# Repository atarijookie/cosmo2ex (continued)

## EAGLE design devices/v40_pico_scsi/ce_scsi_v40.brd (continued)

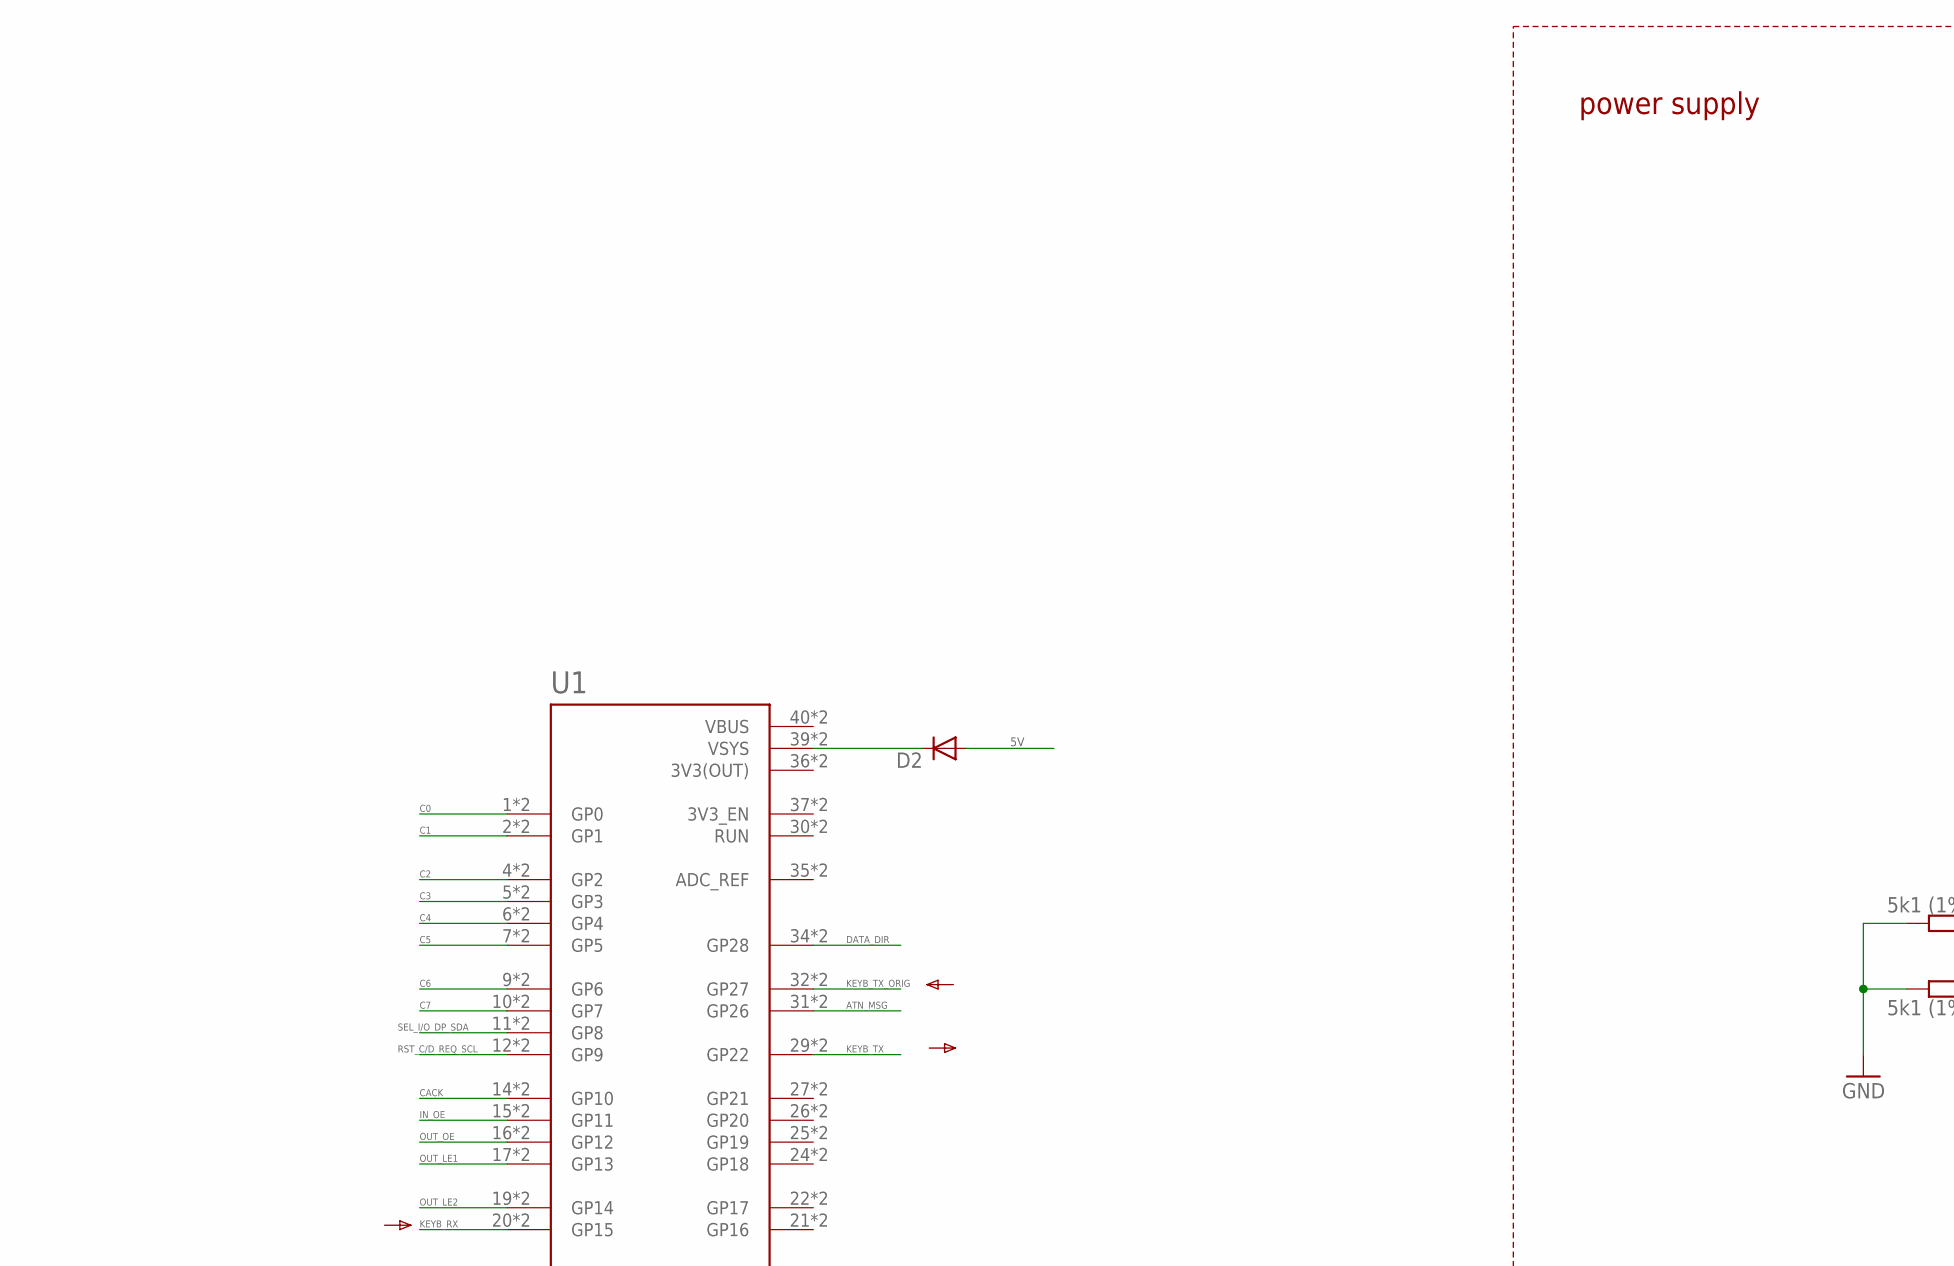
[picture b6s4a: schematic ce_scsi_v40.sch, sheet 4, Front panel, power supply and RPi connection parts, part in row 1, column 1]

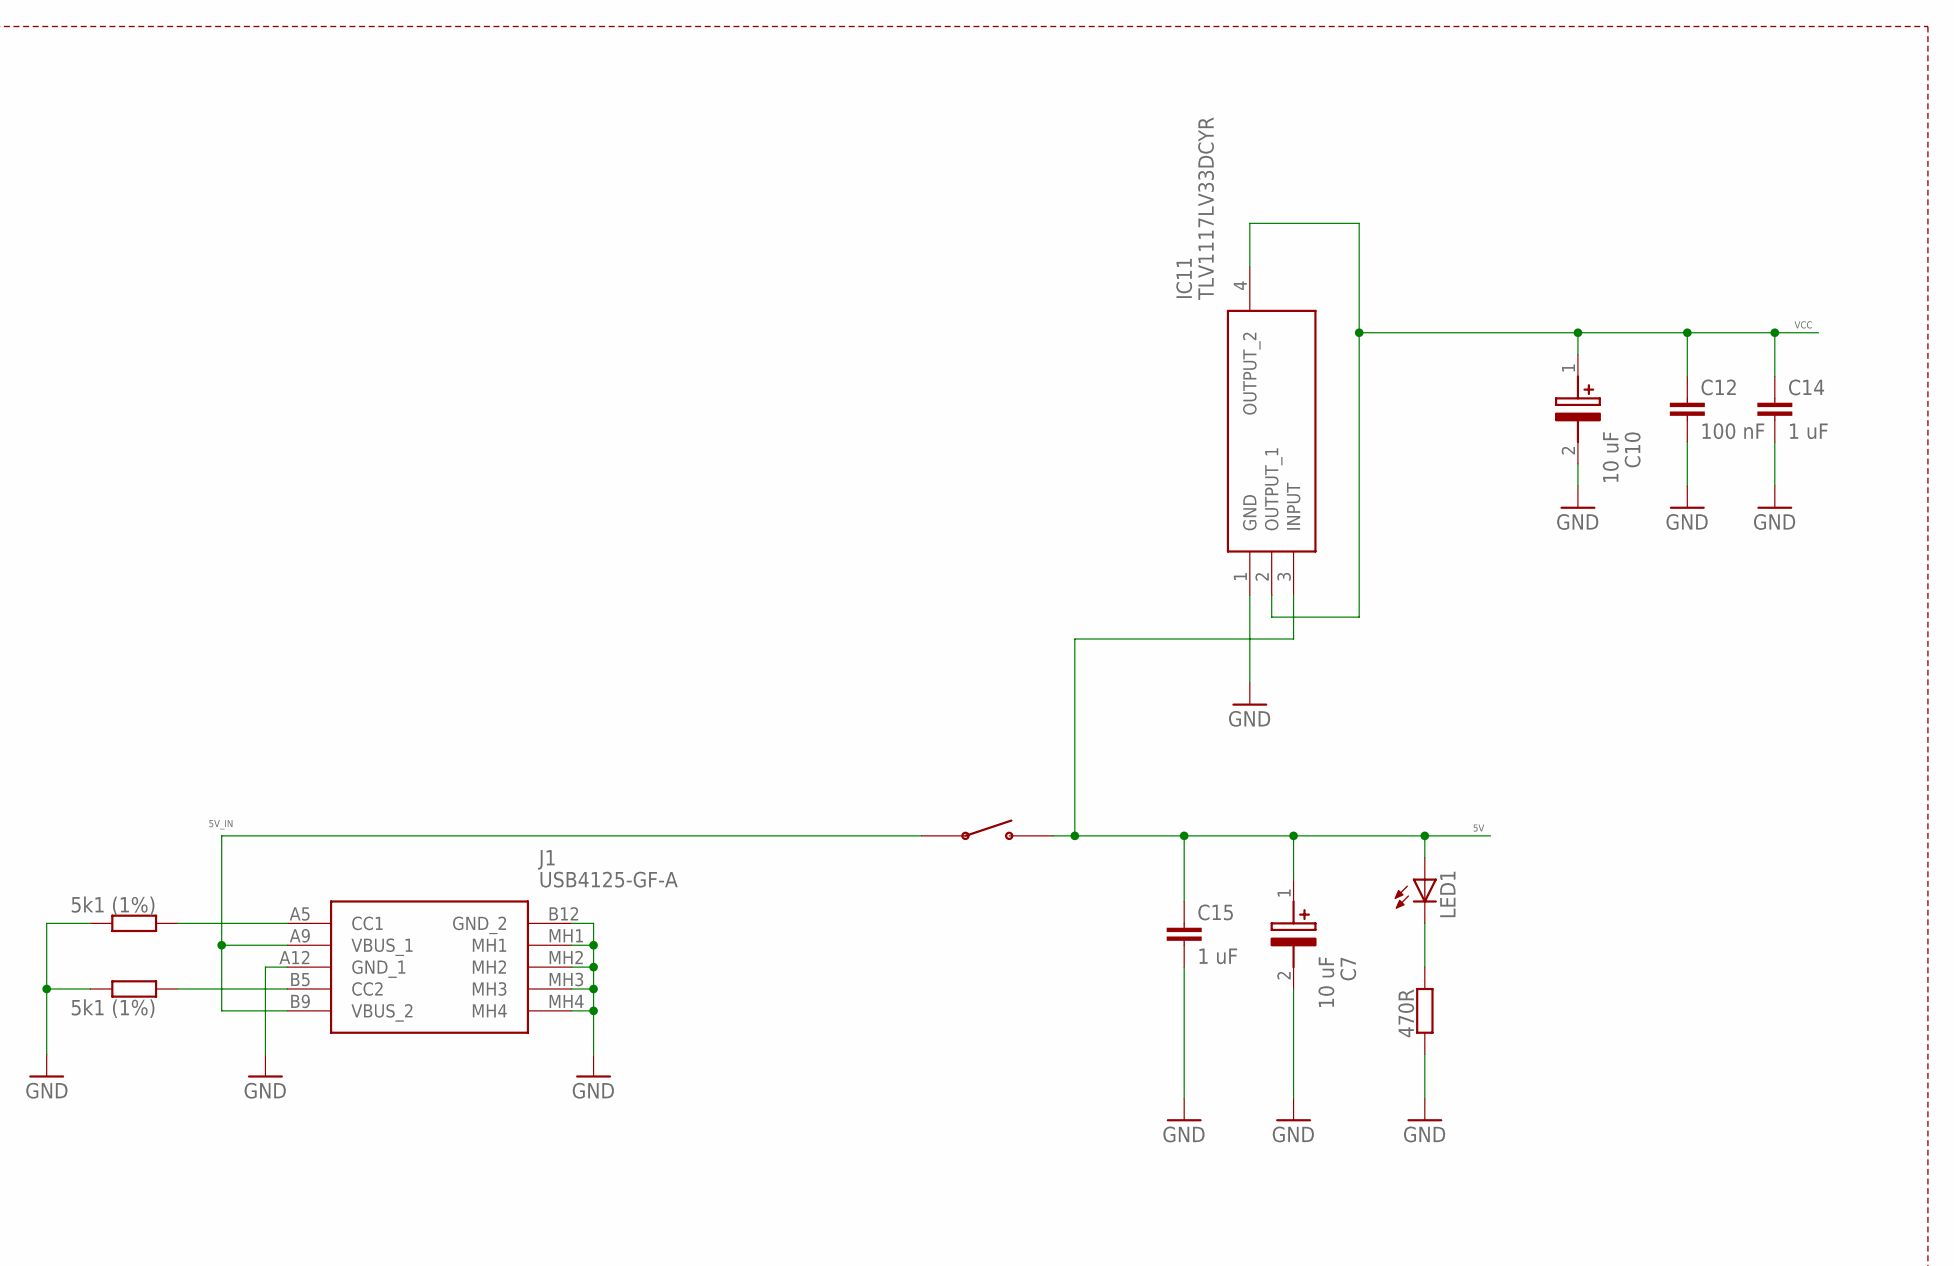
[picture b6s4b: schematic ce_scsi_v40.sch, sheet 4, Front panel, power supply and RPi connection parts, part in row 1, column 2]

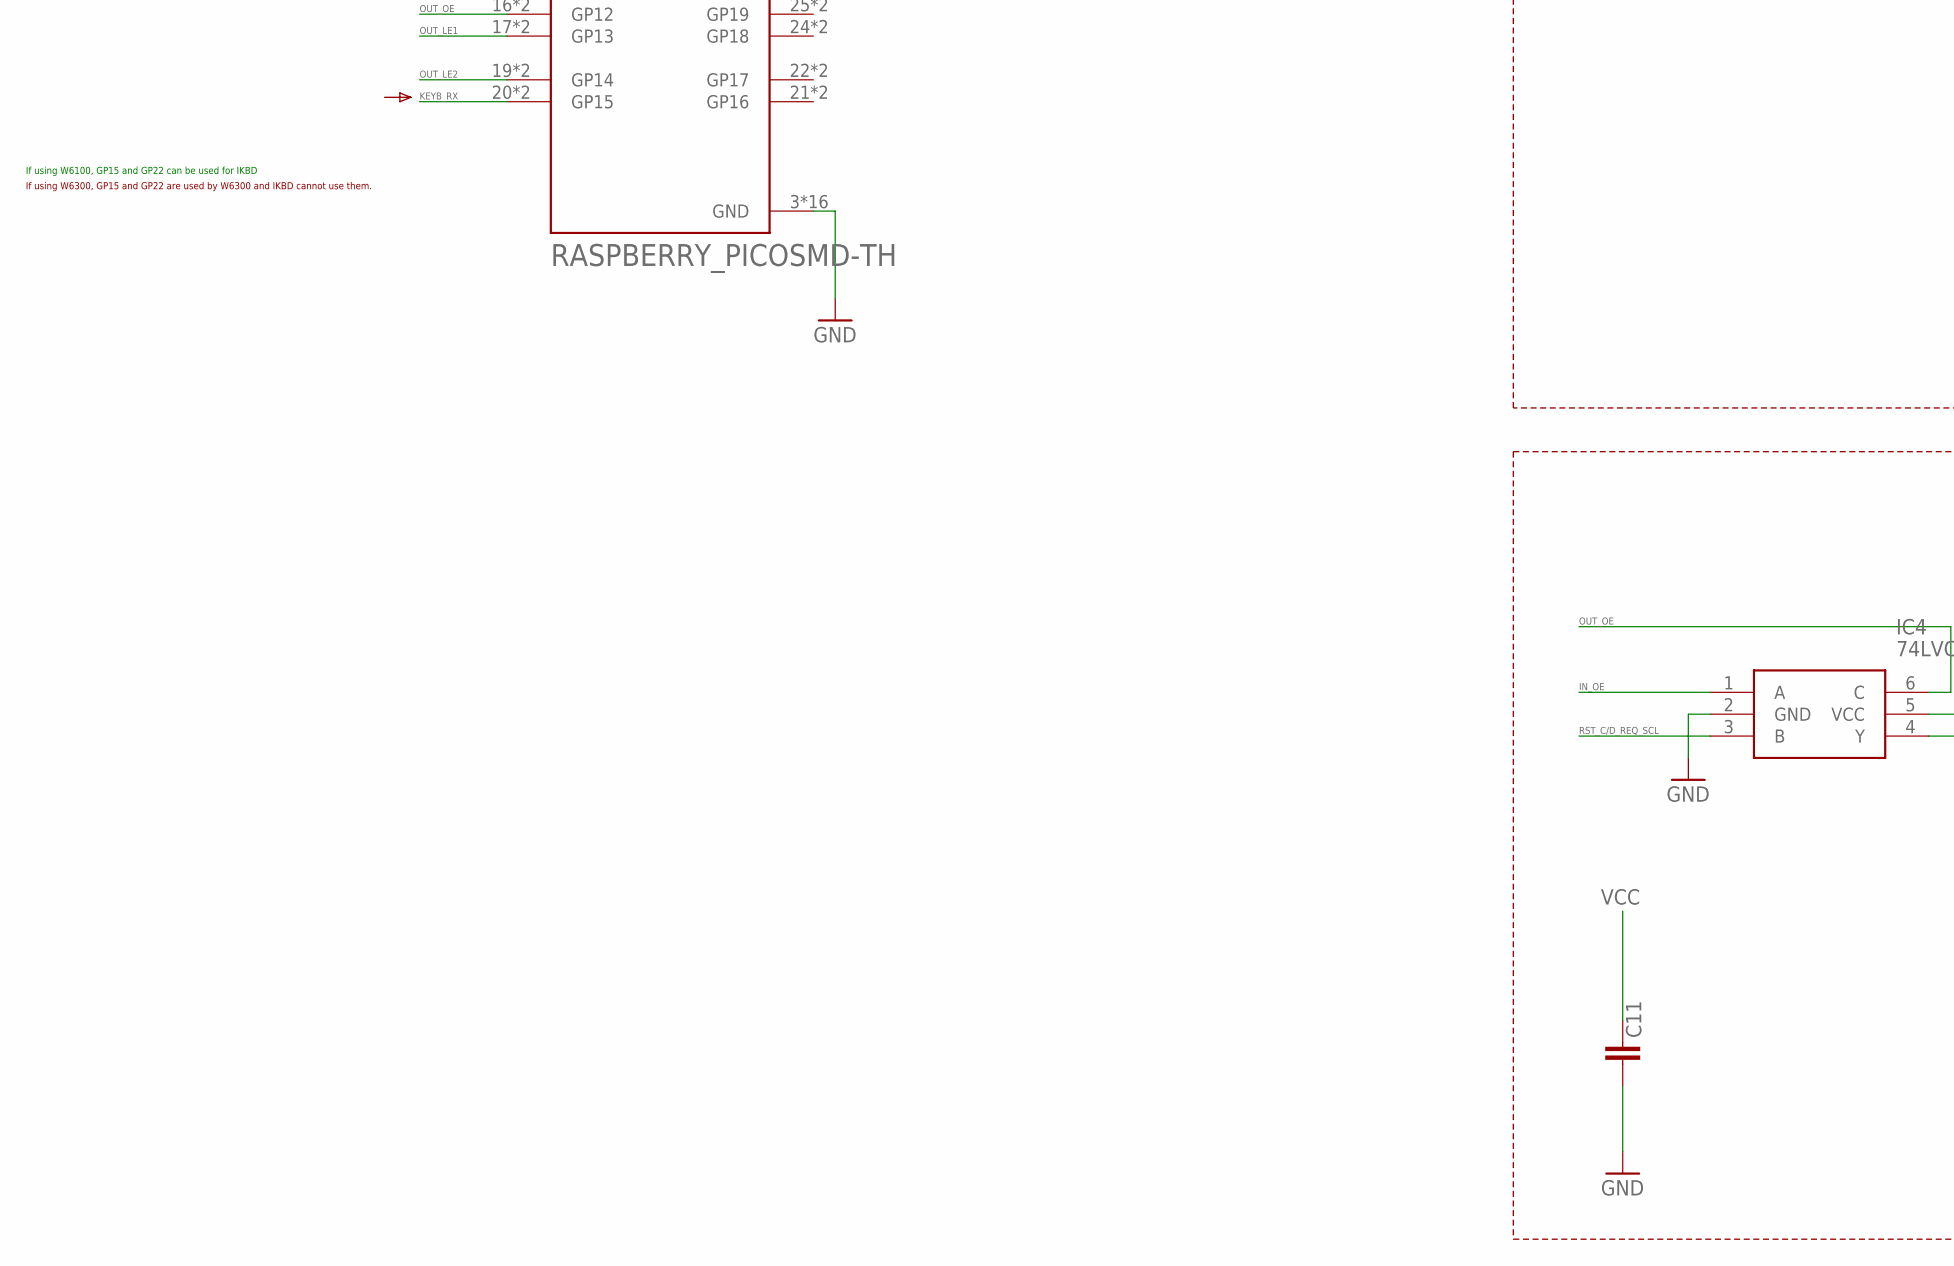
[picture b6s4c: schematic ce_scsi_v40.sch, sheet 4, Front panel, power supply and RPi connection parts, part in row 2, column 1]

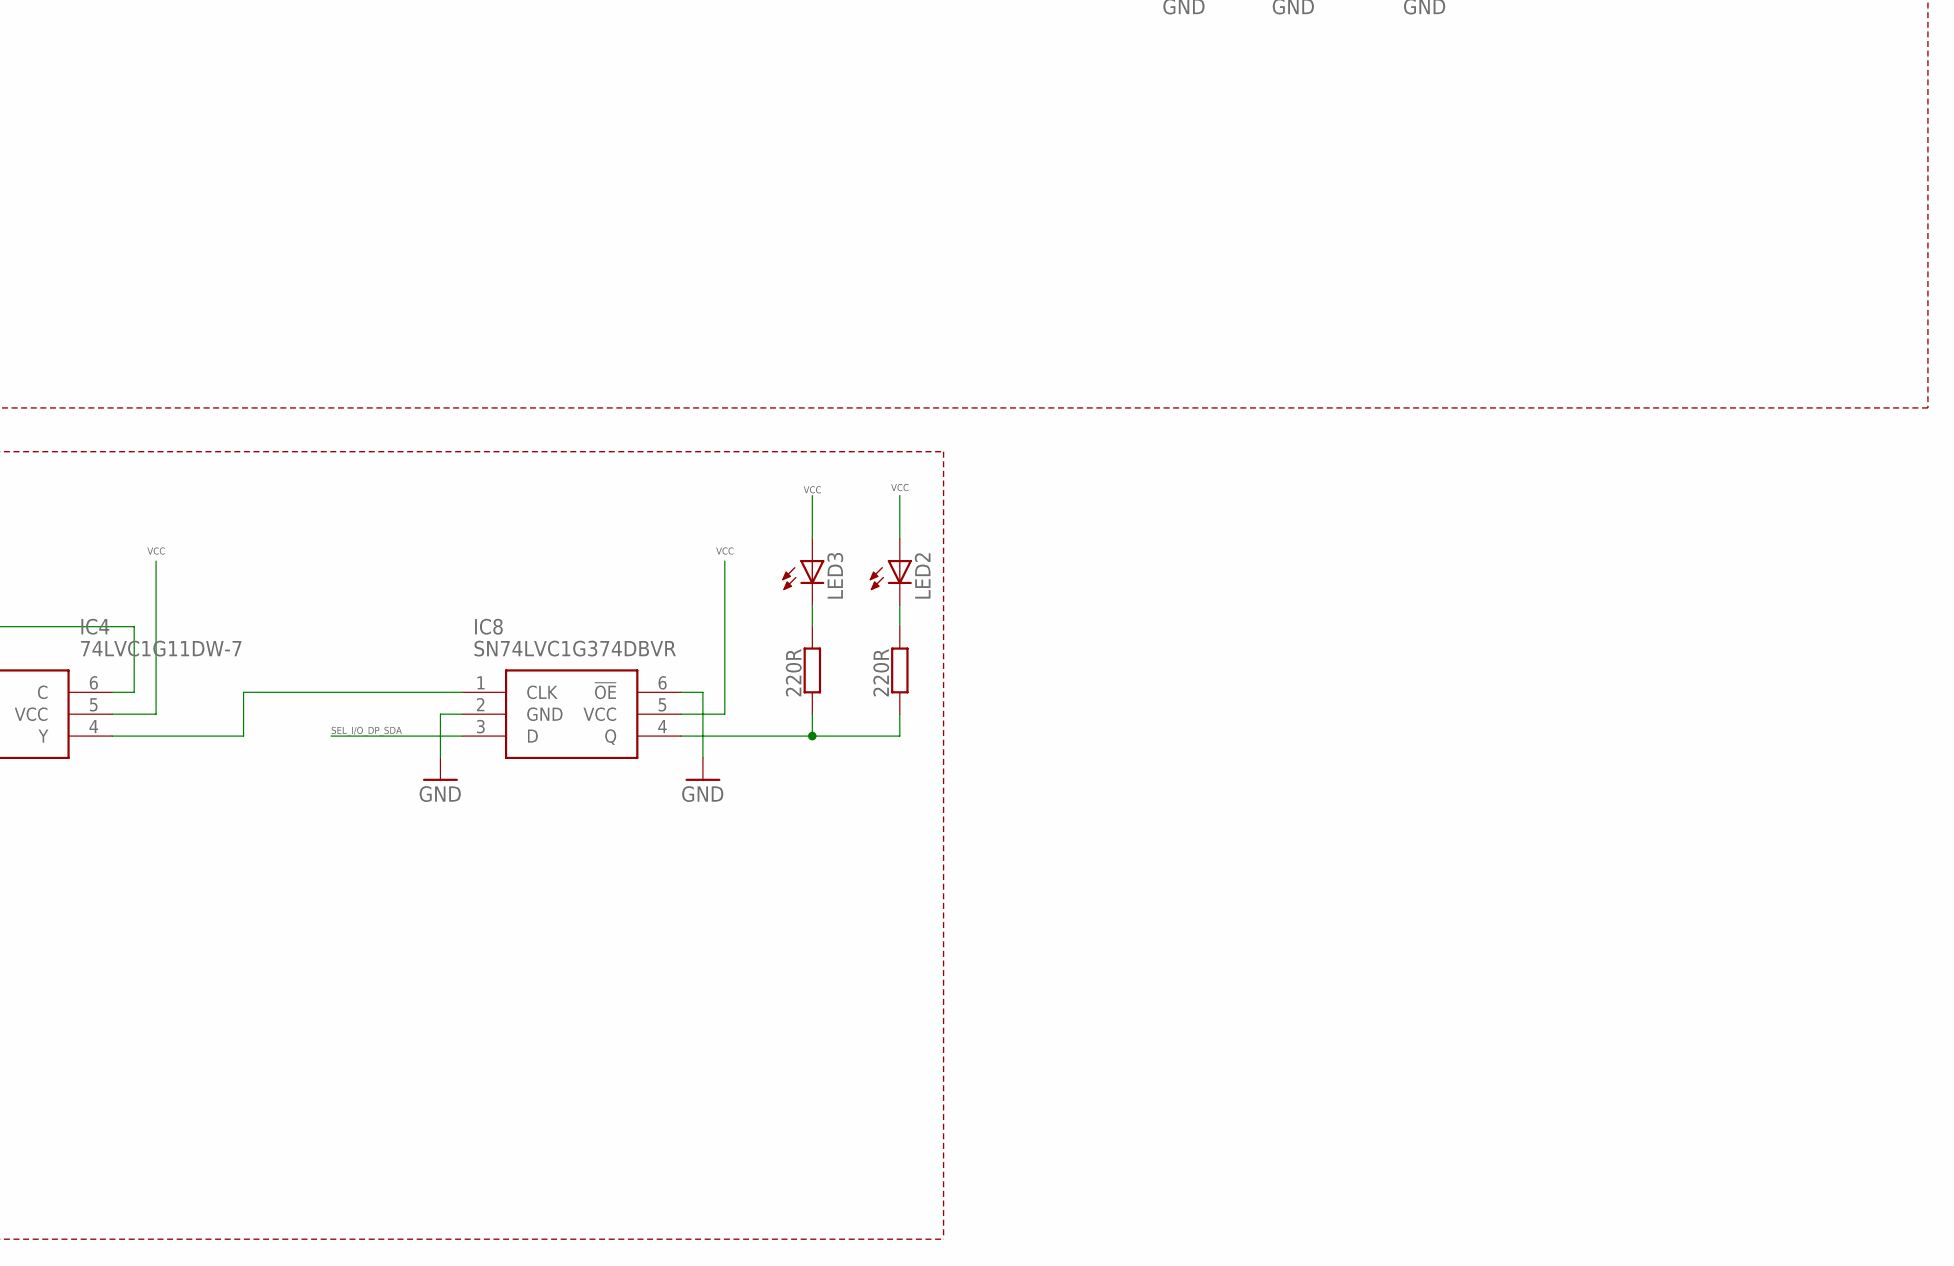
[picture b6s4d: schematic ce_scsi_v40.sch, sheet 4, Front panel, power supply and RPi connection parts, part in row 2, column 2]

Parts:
C7: 10 uF; CAPPM3528X210N
C10: 10 uF; CAPPM3528X210N; MANUFACTURER_PART_NUMBER 293D106X9016B2TE3
C11, C12: 100 nF; C0603
C14, C15: 1 uF; C0805
D2: SK110-DIO; DO214AC
IC4: 74LVC1G11DW-7; SOT65P210X110-6N
IC8: SN74LVC1G374DBVR; SOT95P280X145-6N
IC11: TLV1117LV33DCYR; SOT230P700X180-4N
J1: USB4125-GF-A; USB4125GFA
LED1, LED2, LED3: LEDSML0603; SML0603
R14, R17: 5k1 (1%); R0603
R18: 470R; R0603
R20, R21: 220R; R0603
U1: RASPBERRY_PICOSMD-TH; PICO-PKG
U$1: RSSM1011C3BK

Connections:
3V3(OUT): U1.36 (3V3(OUT)), U1.P$36 (3V3(OUT))
5V: C7.1 (+), C15.1, D2.A, IC11.3 (INPUT), LED1.A, U$1.P$2; also elsewhere on the board
5V_IN: J1.A9 (VBUS_1), J1.B9 (VBUS_2), U$1.P$1
ATN_MSG: U1.31 (GP26), U1.P$31 (GP26); also elsewhere on the board
C0: U1.1 (GP0), U1.P$1 (GP0); also elsewhere on the board
C1: U1.2 (GP1), U1.P$2 (GP1); also elsewhere on the board
C2: U1.4 (GP2), U1.P$4 (GP2); also elsewhere on the board
C3: U1.5 (GP3), U1.P$5 (GP3); also elsewhere on the board
C4: U1.6 (GP4), U1.P$6 (GP4); also elsewhere on the board
C5: U1.7 (GP5), U1.P$7 (GP5); also elsewhere on the board
C6: U1.9 (GP6), U1.P$9 (GP6); also elsewhere on the board
C7: U1.10 (GP7), U1.P$10 (GP7); also elsewhere on the board
CACK: U1.14 (GP10), U1.P$14 (GP10); also elsewhere on the board
DATA_DIR: U1.34 (GP28), U1.P$34 (GP28); also elsewhere on the board
GND: C7.2 (-), C10.2 (-), C11.2, C12.2, C14.2, C15.2, IC4.2 (GND), IC8.2 (GND), IC8.6 (!OE), IC11.1 (GND), J1.A12 (GND_1), J1.B12 (GND_2), J1.MH1, J1.MH2, J1.MH3, J1.MH4, R14.2, R17.2, R18.2, U1.3 (GND), U1.8 (GND), U1.13 (GND), U1.18 (GND), U1.23 (GND), U1.28 (GND), U1.33 (GND), U1.38 (GND), U1.P$3 (GND), U1.P$8 (GND), U1.P$13 (GND), U1.P$18 (GND), U1.P$23 (GND), U1.P$28 (GND), U1.P$33 (GND), U1.P$38 (GND); also elsewhere on the board
IN_OE: IC4.1 (A), U1.15 (GP11), U1.P$15 (GP11); also elsewhere on the board
KEYB_RX: U1.20 (GP15), U1.P$20 (GP15); also elsewhere on the board
KEYB_TX: U1.29 (GP22), U1.P$29 (GP22); also elsewhere on the board
KEYB_TX_ORIG: U1.32 (GP27), U1.P$32 (GP27); also elsewhere on the board
unnamed: J1.B5 (CC2), R14.1
unnamed: J1.A5 (CC1), R17.1
unnamed: IC4.4 (Y), IC8.1 (CLK)
unnamed: IC8.4 (Q), R20.2, R21.2
unnamed: LED1.C, R18.1
unnamed: LED2.C, R20.1
unnamed: LED3.C, R21.1
unnamed: D2.C, U1.39 (VSYS), U1.P$39 (VSYS)
OUT_LE1: U1.17 (GP13), U1.P$17 (GP13); also elsewhere on the board
OUT_LE2: U1.19 (GP14), U1.P$19 (GP14); also elsewhere on the board
OUT_OE: IC4.6 (C), U1.16 (GP12), U1.P$16 (GP12); also elsewhere on the board
RST_C/D_REQ_SCL: IC4.3 (B), U1.12 (GP9), U1.P$12 (GP9); also elsewhere on the board
SEL_I/O_DP_SDA: IC8.3 (D), U1.11 (GP8), U1.P$11 (GP8); also elsewhere on the board
VBUS: U1.40 (VBUS), U1.P$40 (VBUS)
VCC: C10.1 (+), C11.1, C12.1, C14.1, IC4.5 (VCC), IC8.5 (VCC), IC11.2 (OUTPUT_1), IC11.4 (OUTPUT_2), LED2.A, LED3.A; also elsewhere on the board

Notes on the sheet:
power supply
If using W6100, GP15 and GP22 can be used for IKBD
If using W6300, GP15 and GP22 are used by W6300 and IKBD cannot use them.

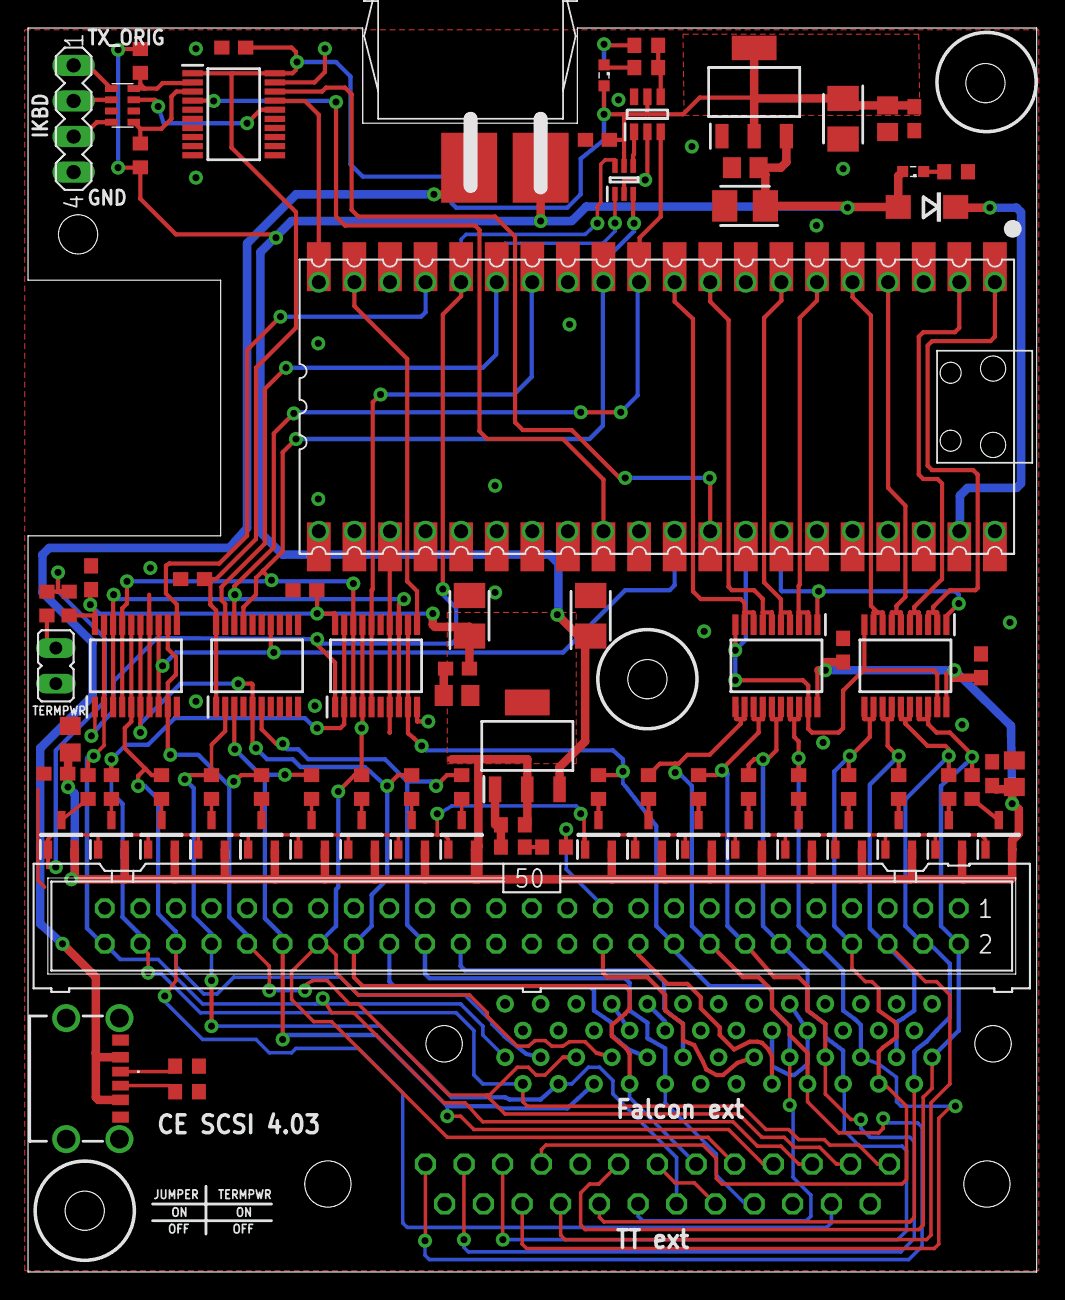
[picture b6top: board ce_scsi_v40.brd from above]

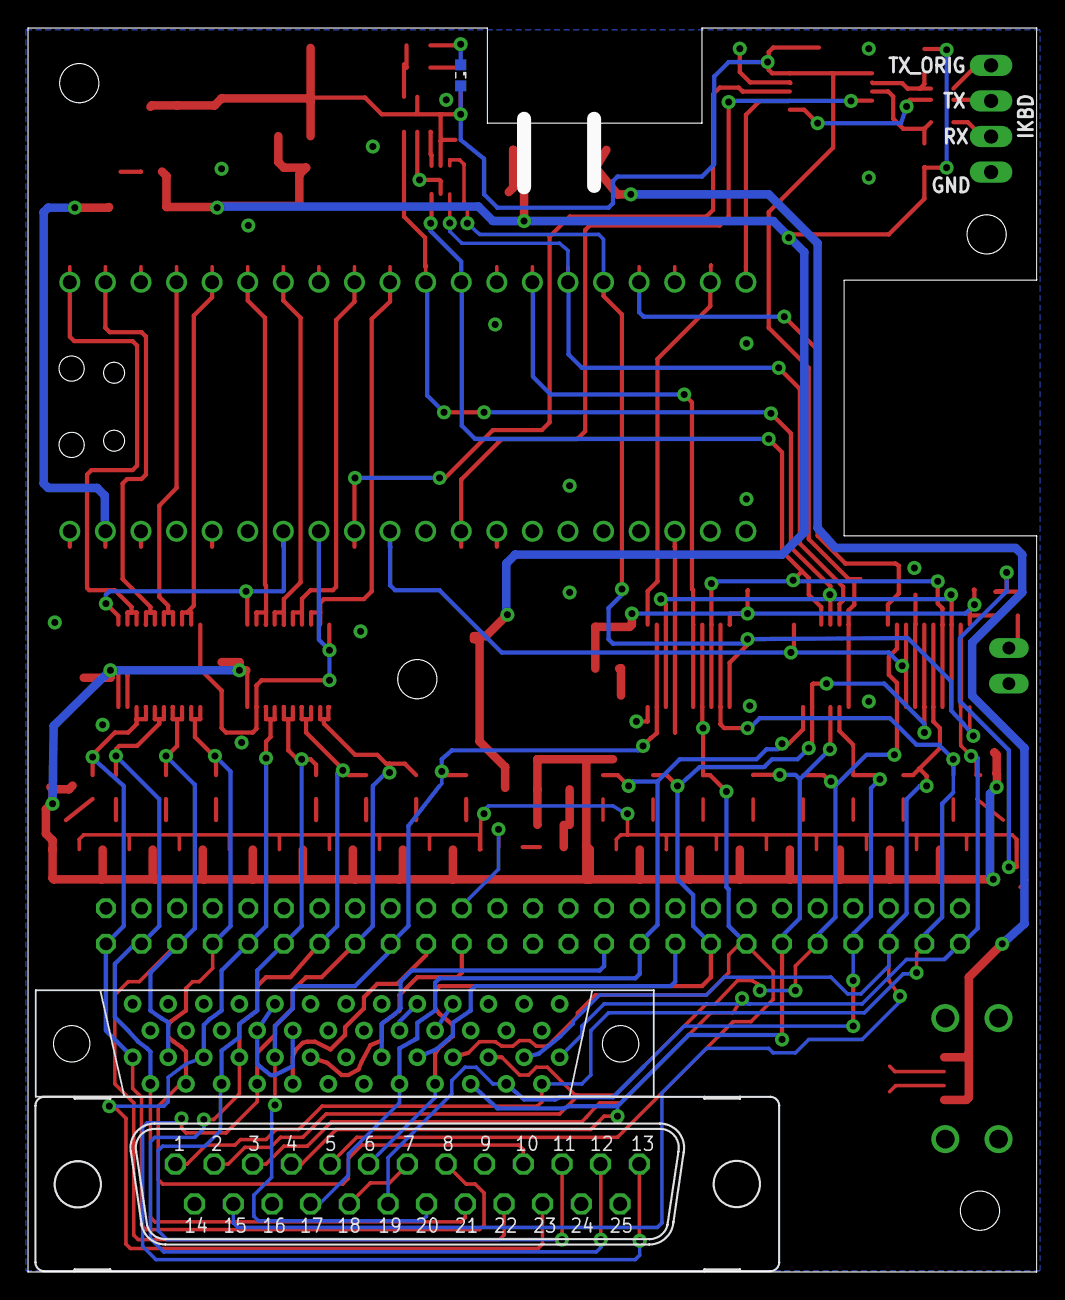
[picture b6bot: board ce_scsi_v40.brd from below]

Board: 2 copper layers, 72.0 x 88.8 mm, 91 parts (3 on the bottom side), 81 nets.

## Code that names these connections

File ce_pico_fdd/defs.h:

#ifndef DEFS_H_
#define DEFS_H_

#include <cstdint>

#define DEBUG_STRINGS   1       // debug() on GP0 (TX0), 115200 baud; 0 = no output, see debug() in utils.cpp
#ifndef MFM_PERF_TEST
#define MFM_PERF_TEST   0       // 1 = track stream timing test next to the real stream, results in the debug log every 5 s, see mfm_perf.h
#endif
#ifndef BUILTIN_IMAGE_TEST
#define BUILTIN_IMAGE_TEST 0    // 1 = the built-in floppy shows all its statuses in a loop (sample values, BUILTIN_TEST_STEP_MS each, then
#endif                          //     no status sector for a step) and never switches to the real image - see builtin_image.h
#define BUILTIN_TEST_STEP_MS 8000
#define FDD_STATUS_LOG  0       // 1 = floppy status in the debug log once a second while the ST uses the drive, see core1StatusReport()

#ifndef TRUE
    #define TRUE 1
#endif

#ifndef FALSE
    #define FALSE 0
#endif

#ifndef MIN
    #define MIN(X,Y)    ((X < Y) ? X : Y)
#endif

#ifndef MAX
    #define MAX(X,Y)    ((X > Y) ? X : Y)
#endif

#define MFM_4US         1
#define MFM_6US         2
#define MFM_8US         3

#define DEV_FEATURE_IKBD    8
#define DEV_FEATURE_FDD     4
#define DEV_FEATURE_SCSI    2
#define DEV_FEATURE_ACSI    1

// commands sent from device to host
#define ATN_FW_VERSION          0x01        // followed by string with FW version (length: 4 WORDs - cmd, v[0], v[1], 0)
#define ATN_SECTOR_WRITTEN      0x03        // sent: 3, side (highest bit) + track #, current sector #
#define ATN_SEND_TRACK          0x04        // send the whole track
#define ATN_SEND_WHOLE_IMAGE    0x05        // send the whole image
#define ATN_GET_IMAGE_LIST      0x06        // page of image names in the folder of the current image - see image_browser.h
#define ATN_INSERT_IMAGE        0x07        // insert image from that folder by name, the host replies with INSERT_IMAGE_*
#define ATN_DEVICE_SETTINGS     0x08        // host -> device only: settings flags (1 B, DEV_SETTING_* in settings.h) from the web UI
#define ATN_LED_COLORS          0x09        // host -> device only: neopixel color while running - R, G, B (3 B), from the web UI

#define INSERT_IMAGE_OK         0           // found, loading - the image follows as on ATN_SEND_WHOLE_IMAGE
#define INSERT_IMAGE_NOT_FOUND  1           // no such image in the folder (anymore)
#define INSERT_IMAGE_FAILED     2           // bad request, or the current image can't be browsed

// commands sent from host to device
#define CMD_WRITE_PROTECT_OFF       0x10
#define CMD_WRITE_PROTECT_ON        0x20
#define CMD_DISK_CHANGE_OFF         0x30
#define CMD_DISK_CHANGE_ON          0x40
#define CMD_GET_FW_VERSION          0x60
#define CMD_SET_DRIVE_ID_0          0x70
#define CMD_SET_DRIVE_ID_1          0x80
#define CMD_CURRENT_TRACK           0x90                            // followed by track #
#define CMD_DRIVE_ENABLED           0xa0
#define CMD_DRIVE_DISABLED          0xb0


///////////////////////////

#define TX_HEADER_SIZE                  10
#define ATN_SENDFWVERSION_LEN_TX        (TX_HEADER_SIZE + 14)       // version (4), features, 0, mac (6), settings flags, 0
#define ATN_SENDTRACK_REQ_LEN_TX        (TX_HEADER_SIZE + 2)

///////////////////////////

#define SPI_PORT spi0

#define PANEL_UART_BAUD     115200


#define PIN_TXD_DEBUG       0
#define PIN_CAPTIVE_BTN     1       // button to 3.3V (H = pressed), long press starts the captive portal - instead of the debug UART RX, which isn't used
#define PIN_NEOPIXEL        1       // the same pin, to LED2 through the AND gate IC6 - output only while sending a frame, see neopixel_pio.cpp
#define PIN_DRIVE_SEL       2
#define PIN_MOT_EN          3
#define PIN_DIR             4
#define PIN_STEP            5
#define PIN_WGATE           6
#define PIN_SIDE1           7
#define PIN_KEYB_TX         8
#define PIN_KEYB_TX_ORIG    9
#define PIN_SCK             10
#define PIN_MOSI            11
#define PIN_MISO            12
#define PIN_CS              13
#define PIN_RDATA           14
#define PIN_DSKCHG          15
#define PIN_PANEL_TX        16      // front panel UART (PIO), see ce_pico_display/protocol.md
#define PIN_PANEL_RX        17
#define PIN_KEYB_RX         18
#define PIN_WPROTECT        19
#define PIN_TRACK00         20
#define PIN_INDEX           21
#define PIN_DENSITY         22
#define PIN_WDATA           26
#define PIN_BEEPER          27      // buzzer with its own generator, H = on, see beeper.h
#define PIN_FLCC_OE         28

#define BIT_IS_H(PIN)   (gpio_get(PIN) != 0)
#define BIT_IS_L(PIN)   (gpio_get(PIN) == 0)
#define BIT_LEVEL(PIN)  ( (gpio_get(PIN) == 0) ? 0 : 1)

#define WRITEBUFFER_SIZE    1300

typedef struct {
    volatile uint8_t side;
    volatile uint8_t track;
    volatile uint8_t sector;
} TDrivePosition;

#define READTRACKDATA_SIZE_BYTES    13800
#define MAX_TRACKS                  90
#define MAX_SECTORS_PER_TRACK       11

#define IMAGE_NOT_LOADED    0
#define IMAGE_REQUESTED     1
#define IMAGE_LOADED        2

#define TAG_WRITE_START 0x80    // start of sector data - sent from MFM streamer
#define TAG_WRITE_END   0xc0    // end of sector data - sent from MFM streamer

#endif /* DEFS_H_ */

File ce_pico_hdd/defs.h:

#ifndef DEFS_H_
#define DEFS_H_

#include <Arduino.h>

#define LOG_MORE    1
#define LOG_LED     1
// #define LOG_UART    1

// DEBUG_TO_IKBD 0 (default): LOG_LED debug output goes to the LED pin (GP25) of the W6100-EVB-Pico.
// DEBUG_TO_IKBD 1: LOG_LED debug output goes to GP22 (KEYB_TX) at 115200 baud instead, IKBD output to the Atari is disabled.
//                  For debugging boards where the LED pin is not reachable.
#ifndef DEBUG_TO_IKBD
    #define DEBUG_TO_IKBD   0
#endif

#ifndef MIN
    #define MIN(X,Y)    ((X < Y) ? X : Y)
#endif

#ifndef MAX
    #define MAX(X,Y)    ((X > Y) ? X : Y)
#endif

#define DEV_FEATURE_IKBD    8
#define DEV_FEATURE_FDD     4
#define DEV_FEATURE_SCSI    2
#define DEV_FEATURE_ACSI    1

#define CMD_TIMEOUT_SECS_PER_MB 3
#define CMD_TIMEOUT_ONESECOND   1000
#define CMD_TIMEOUT_SHORT       (CMD_TIMEOUT_ONESECOND / 2)     // this period will be 0.5 second
#define CMD_TIMEOUT_LONG        (CMD_TIMEOUT_ONESECOND * 3)     // this period will be 3.0 second

// commands sent from device to host
#define ATN_FW_VERSION                      0x01                                // followed by string with FW version (length: 4 uint16_ts - cmd, v[0], v[1], 0)
#define ATN_ACSI_COMMAND                    0x02
// #define ATN_READ_MORE_DATA                  0x03
#define ATN_WRITE_MORE_DATA                 0x04
// #define ATN_GET_STATUS                      0x05

// commands sent from host to device
#define CMD_ACSI_CONFIG                     0x10
#define CMD_DATA_WRITE                      0x20
#define CMD_DATA_READ_WITH_STATUS           0x30
#define CMD_SEND_STATUS                     0x40
#define CMD_DATA_READ_WITHOUT_STATUS        0x50
#define CMD_FLOPPY_CONFIG                   0x70
#define CMD_FLOPPY_SWITCH                   0x80
#define CMD_DATA_MARKER                     0xda
#define CMD_LED_COLORS                      0xe0    // neopixel colors while running: ACSI R, G, B, SCSI R, G, B (6 B), from the web UI

// ACSI only - for the SLM laser printer emulation on host (ce_cores/hdd/slm/)
#define CMD_PIO_READ                        0x90    // send the payload bytes to ST with CS / INT handshake (status + EXTENDED STATUS PHASE), then wait for next command
#define CMD_PIO_WRITE                       0xc0    // get N bytes from ST with CS / INT handshake (EXTENDED COMMAND PHASE), sent to host as on DMA write
#define CMD_DATA_WRITE_PACED                0xd0    // DMA write in printer scan line bursts, see onDataWritePaced()
#define DATA_WRITE_PACED_PAYLOAD_SIZE       16

// these states define if the device should get command or transfer data
#define STATE_GET_COMMAND                       0
// #define STATE_SEND_COMMAND                   1
#define STATE_WAIT_COMMAND_RESPONSE             2
#define STATE_DATA_READ_WITH_STATUS             3
#define STATE_DATA_READ_WITHOUT_STATUS          4
#define STATE_DATA_WRITE                        5
#define STATE_WAIT_FOR_STATUS_ARRIVAL           6
#define STATE_READ_STATUS                       7

#define STATE_SEND_FW_VER                       10
#define STATE_SEND_WRITE_MORE_DATA              11
#define STATE_DATA_READ                         12
#define STATE_PIO_READ                          13
#define STATE_PIO_WRITE                         14
#define STATE_DATA_WRITE_PACED                  15

///////////////////////////

#define ATN_VARIABLE_LEN                0xffff

#define TX_HEADER_SIZE                  10
#define ATN_SENDFWVERSION_LEN_TX        (TX_HEADER_SIZE + 12)
#define ATN_SENDACSICOMMAND_LEN_TX      (TX_HEADER_SIZE + 14)

///////////////////////////
// pins of the v40_pico_hdd board (devices/v40_pico_hdd) - one PCB, assembled either as ACSI or as SCSI variant.
// Most of the GPIOs have a different function in each variant, the variant is read from PIN_VARIANT_STRAP on boot.

// common for both variants
#define PIN_D0              0       // D0..D7 through IC2/IC3 (both variants), DATA_DIR sets their direction
#define PIN_D1              1
#define PIN_D2              2
#define PIN_D3              3
#define PIN_D4              4
#define PIN_D5              5
#define PIN_D6              6
#define PIN_D7              7
#define PIN_ACK             10      // in  - SCSI: CACK (through latch IC203), ACSI: ACK (through IC101)
#define PIN_DATA_DIR        28      // out

#define PIN_NEOPIXEL        9       // out - ACSI only: to the WS2812 through the AND gate IC6 (5V level shifter), its other input is H (R151).
                                    //       SCSI: the neopixel data is OUT_LE1 on IC6.A, gated by OUT_LE2 on IC6.B
#define PIN_VARIANT_STRAP   26      // in on boot - H: ACSI (R125 pull-up), L: SCSI (R225 pull-down)

#define PIN_KEYB_RX         15
#define PIN_KEYB_TX         22
#define PIN_KEYB_TX_ORIG    27

#if DEBUG_TO_IKBD
    #define PIN_DEBUG_TX    PIN_KEYB_TX     // with LOG_LED + DEBUG_TO_IKBD - debug strings on KEYB_TX, IKBD output disabled
#else
    #define PIN_DEBUG_TX    25              // with LOG_LED - the LED pin of the module, not on its edge pins
#endif

// SCSI variant
#define PIN_SEL_IO_DP_DS    8
#define PIN_RST_CD_REQ_CP   9
#define PIN_IN_OE           11      // out
#define PIN_OUT_OE          12      // out
#define PIN_OUT_LE1         13      // out
#define PIN_OUT_LE2         14      // out
#define PIN_ATN_MSG         26

// ACSI variant
#define PIN_A1              8       // in
#define PIN_CS              11      // in
#define PIN_INT             12      // out
#define PIN_DRQ             13      // out
#define PIN_RESET           14      // in

#define DATA_PINS_MASK          ((1 << PIN_D0) | (1 << PIN_D1) | (1 << PIN_D2) | (1 << PIN_D3) | (1 << PIN_D4) | (1 << PIN_D5) | (1 << PIN_D6) | (1 << PIN_D7))
#define SCSI_DATA_PINS_MASK     (DATA_PINS_MASK | (1 << PIN_SEL_IO_DP_DS))      // data + DP
#define SCSI_HANDSHAKE_PINS_MASK    ((1 << PIN_RST_CD_REQ_CP) | (1 << PIN_ACK))
#define ACSI_HANDSHAKE_OUT_PINS     ((1 << PIN_DRQ) | (1 << PIN_INT))

#define BIT_IS_H(PIN)   (gpio_get(PIN) != 0)
#define BIT_IS_L(PIN)   (gpio_get(PIN) == 0)
#define BIT_LEVEL(PIN)  ( (gpio_get(PIN) == 0) ? 0 : 1)

#define BIT_SET(PIN)    gpio_put(PIN, true)
#define BIT_CLR(PIN)    gpio_put(PIN, false)

#endif /* DEFS_H_ */

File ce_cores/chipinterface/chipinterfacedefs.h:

#ifndef __CHIPINTERFACEDEFS_H__
#define __CHIPINTERFACEDEFS_H__

#include <stdint.h>
#include <sys/socket.h>
#include <netinet/in.h>

// types of chip interface, as returned by the individual chip interface classes
#define CHIP_IF_DUMMY   -1
#define CHIP_IF_V1_V2   1
#define CHIP_IF_V3      3
#define CHIP_IF_V4      4
#define CHIP_IF_RASCSI  8
#define CHIP_IF_NETWORK 9

//---------------------------------------------
// ATN codes: commands sent from device to host (in header, see BufferedReader)

#define ATN_ANY                         0xff        // this is used only on host to wait for any ATN

// Hans (HDD)
#define ATN_FW_VERSION                  0x01        // followed by FW version, mac, features (shared with Franz, same code)
#define ATN_ACSI_COMMAND                0x02
#define ATN_READ_MORE_DATA              0x03
#define ATN_WRITE_MORE_DATA             0x04
// ATN_GET_STATUS                       0x05        // not used by current firmware

// Franz (FDD) - ATN_FW_VERSION (0x01) as above
#define ATN_SECTOR_WRITTEN              0x03        // sent: 3, side (highest bit) + track #, current sector #
#define ATN_SEND_TRACK                  0x04        // send the whole track
#define ATN_SEND_WHOLE_IMAGE            0x05        // send the whole image
#define ATN_GET_IMAGE_LIST              0x06        // page of image names in the folder of the current image, see fdd/imagelist.h
                                                    //   device: start (4 B, 0xffffffff = around the current image), count (2 B)
                                                    //   host (the reply, and on its own when the list / current image changes):
                                                    //   gen, total, current index, start (4 B each), count (2 B), count * [len (1 B), name]
#define ATN_INSERT_IMAGE                0x07        // insert image from that folder by name
                                                    //   device: gen, index (4 B each), name len (1 B), name
                                                    //   host: status (1 B) - INSERT_IMAGE_*

#define ATN_DEVICE_SETTINGS             0x08        // host -> device only: settings flags (1 B, DEV_SETTING_*) changed in the web UI;
                                                    //   the device reports its flags in the FW report (byte 12 of the data)

#define ATN_LED_COLORS                  0x09        // host -> device only: neopixel color while running - R, G, B (3 B), from the web UI
                                                    //   (global settings, LED_COLOR_SETTING_*); sent once per connection and on change

#define DEV_SETTING_IKBD                0x01        // device IKBD (keyboard / mouse via the host) enabled
#define DEV_SETTING_BEEP_ON_STEP        0x02        // beeper clicks on every head step

#define INSERT_IMAGE_OK                 0           // found, loading - the image follows as on ATN_SEND_WHOLE_IMAGE
#define INSERT_IMAGE_NOT_FOUND          1           // no such image in the folder (anymore)
#define INSERT_IMAGE_FAILED             2           // bad request, or the current image can't be browsed (no image, special image)

//---------------------------------------------
// CMD codes: commands sent from host to device

// Hans (HDD)
#define CMD_ACSI_CONFIG                 0x10
#define CMD_DATA_WRITE                  0x20
#define CMD_DATA_READ_WITH_STATUS       0x30
#define CMD_SEND_STATUS                 0x40
#define CMD_DATA_READ_WITHOUT_STATUS    0x50
#define CMD_FLOPPY_CONFIG               0x70
#define CMD_FLOPPY_SWITCH               0x80
#define CMD_GET_LICENSE                 0xa0
#define CMD_DO_UPDATE                   0xb0
#define CMD_DATA_MARKER                 0xda
#define CMD_LED_COLORS                  0xe0        // neopixel colors while running: ACSI R, G, B, SCSI R, G, B (6 B) - the device
                                                    //   uses the one of its variant; sent once per connection and on change

// Hans (HDD) - ACSI only, for the SLM laser printer emulation (hdd/slm/)
#define CMD_PIO_READ                    0x90        // send the payload bytes to ST one by one with CS / INT handshake (status + EXTENDED STATUS PHASE), then wait for the next command; no payload = just wait for the next command
#define CMD_PIO_WRITE                   0xc0        // get N bytes from ST with CS / INT handshake (EXTENDED COMMAND PHASE), N in 24 bits; data comes back as on CMD_DATA_WRITE
#define CMD_DATA_WRITE_PACED            0xd0        // get N bytes from ST using DMA, in bursts of one printer scan line (payload: see ChipInterface::hdd_recvDataPaced_start())
#define DATA_WRITE_PACED_PAYLOAD_SIZE   16
#define PIO_READ_MAX_LEN                64          // device waits for at most this many payload bytes (PAYLOAD_MAX_WAIT_SIZE in ce_pico_hdd)

// Franz (FDD)
#define CMD_WRITE_PROTECT_OFF           0x10
#define CMD_WRITE_PROTECT_ON            0x20
#define CMD_DISK_CHANGE_OFF             0x30
#define CMD_DISK_CHANGE_ON              0x40
#define CMD_SET_DRIVE_ID_0              0x70
#define CMD_SET_DRIVE_ID_1              0x80
#define CMD_DRIVE_ENABLED               0xa0
#define CMD_DRIVE_DISABLED              0xb0

//---------------------------------------------
// sizes

#define COMMAND_SIZE            10
#define ACSI_CMD_SIZE           14
#define WRITTENMFMSECTOR_SIZE   2048
#define TX_RX_BUFF_SIZE         600

// Most of the normal games have tracks from 11000 bytes to 12019 bytes of encoded stream.
// With Bad_Brew_Crew/BBC11.ZIP (11 sectors per track?) the resulting stream was 13205 bytes big, I didn't see anything more yet (but there might be something bigger).
// In theory the 11 sectors per track could be up to 13720 bytes big, so 13800 should be enough here.
// In case something bigger appears (e.g. 12 sectors per track), consider shortening GAP 2, GAP 3a, GAP 3B, GAP 4, which take 774 bytes before encoding, 1548 bytes after encoding,
// so if more space for real data would be needed, some adaptive reducing of GAPs sizes could be added (to a point where WD1772 still considers those GAPs to be valid to catch the sync there)
#define MFM_STREAM_SIZE         13800

#define MAKEWORD(A, B)  ( (((uint16_t)A)<<8) | ((uint16_t)B) )

#define HDD_FW_RESPONSE_LEN     12
#define FDD_FW_RESPONSE_LEN     8

#define FW_RESPONSE_LEN_BIGGER  ((HDD_FW_RESPONSE_LEN > FDD_FW_RESPONSE_LEN) ? HDD_FW_RESPONSE_LEN : FDD_FW_RESPONSE_LEN)

#define INBUF_SIZE  (WRITTENMFMSECTOR_SIZE + 8)

#define SYNC_TAG_HDD    0xc050d1c5
#define SYNC_TAG_FDD    0xc0500fdd

#define MAX_CLIENTS     8

#endif
